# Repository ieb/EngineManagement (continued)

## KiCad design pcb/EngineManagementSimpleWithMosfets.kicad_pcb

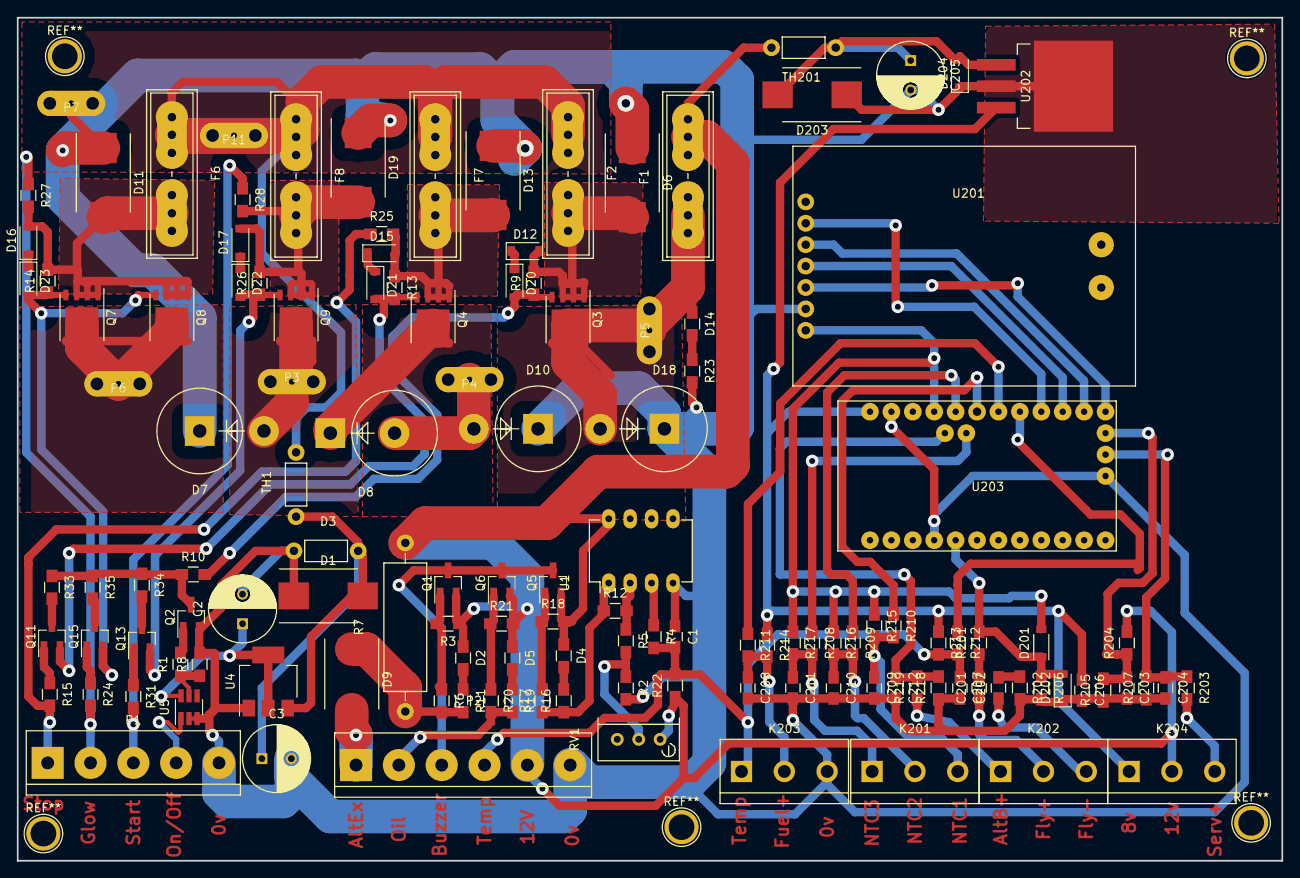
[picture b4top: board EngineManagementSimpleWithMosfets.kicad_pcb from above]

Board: 2 copper layers, 150.0 x 100.0 mm, 131 parts (0 on the bottom side), 77 nets.

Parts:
C1, C201, C202, C206, C207, C208, C209, C210, C211: 10nF; C_0805_HandSoldering
C2, C3: 10uF; C_Radial_D8_L11.5_P3.5
C203, C204, C212: 1nF; C_0805_HandSoldering
C205: 100uF; C_Radial_D8_L11.5_P3.5
D1, D6, D11, D13, D19, D203: SMBJ30CA-TR TSV; DO-214AB_Handsoldering
D2: ChargeWarn; R_0805_HandSoldering
D3: 10A100V; Resistor_Horizontal_RM7mm
D4: TempWarn; R_0805_HandSoldering
D5: OilWarn; R_0805_HandSoldering
D7, D18: 5A 600V; Diode_P600_Vertical_AnodeUp
D8: 10A 600V; Diode_P600_Vertical_KathodeUp
D9: 1A 40V; DO-214AB
D10: 10A 600V; Diode_P600_Vertical_AnodeUp
D12, D15, D16: ZENER; D_SOD-123
D14: PowerOn; R_0805_HandSoldering
D17: 10V Zeener; D_SOD-123
D20, D21, D22, D23: 1N4001; D_SOD-123
D201: 1N5819; SOD-123
D202, D204: 1N5819; D_SOD-123
F1: FUSE 5A; BladeFuse-CarType
F2: FUSE 30A; BladeFuse-CarType
F6, F8: FUSE 40A; BladeFuse-CarType
F7: FUSE 15A; BladeFuse-CarType
K201: Temps; bornier3
K202: FuelCool; bornier3
K203: FuelCoolAlt; bornier3
K204: Supply; bornier3
P1: VPButtons; bornier5
P2: ToEngine; bornier6
P3: StarterSolenoidT30; CrimpBlade
P4: StopSolenoid; CrimpBlade
P5: 12VSwitchedPower; CrimpBlade
P6: GlowPlugs; CrimpBlade
P7: 0v; CrimpBlade
P11: Battery+; CrimpBlade
Q1, Q5, Q6: BC807; SOT-23_Handsoldering
Q2: BS170; SOT-23_Handsoldering
Q3, Q4, Q7, Q8, Q9: SI7137; Si7137PowerPak
Q11, Q13, Q15: BS250P; SOT-23_Handsoldering
R1, R15, R24, R31: 100R; R_0805_HandSoldering
R2: 330R; R_0805_HandSoldering
R3, R4, R5, R8, R9, R17, R21, R25: 10K; R_0805_HandSoldering
R6, R18, R20, R27, R28: 2.2K; R_0805_HandSoldering
R7: 10R; Resistor_Horizontal_RM20mm
R10, R33, R34, R35: 220R; R_0805_HandSoldering
R11, R13, R14, R16, R19, R22, R23, R26, R213, R214: 1K; R_0805_HandSoldering
R12: 10M; R_0805_HandSoldering
R201, R202: 47K; R_0805_HandSoldering
R203, R204, R219: 1M; R_0805_HandSoldering
R205, R207, R218: 470K; R_0805_HandSoldering
R206, R208, R209, R210, R211, R212: 100K; R_0805_HandSoldering
R215, R216, R217: 4.7K; R_0805_HandSoldering
RV1: 20K; Potentiometer_Bourns_3296W_3-8Zoll_Inline_ScrewUp
TH1: THERMISTOR; Resistor_Horizontal_RM7mm
TH201: 500mA Thermistor; Resistor_Horizontal_RM7mm
U1: LM358; DIP-8_W7.62mm_LongPads
U4: NCP1117ST50T3G; SOT-223-3Lead_TabPin2
U5: Max16054; SOT-23-6_Handsoldering
U201: MCP2515Shield; MCP2515Board
U202: LM7808CT; TO-263-3Lead
U203: ArdinoMinPro; ArduinoProMini

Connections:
5V150mA: D201.2, R215.1, R216.1, R217.1, U201.7, U203.21
8V: C206.1, K204.1, R213.1, R214.1, U202.3, U203.24
12vSwitched: D2.1, D4.1, D5.1, F1.2, K204.2, P2.5, Q1.2, Q5.2, Q6.2, R3.1, R7.2, R18.2, R21.2, R22.1, R204.2, RV1.1, TH201.2, U1.8
AlternatorB+: K202.1, R219.1
AlternatorExcitation: D9.2, P2.1
Battery+: F2.1, F6.1, F7.1, F8.1, P11.1, TH1.2
Buzzer: P2.3, Q1.3, Q5.3, Q6.3
CANCS: U201.5, U203.13
CoolantTemp: C1.2, C207.1, K203.1, P2.4, R4.2, R22.2, R212.2, R213.2
Enable: Q2.3, R10.1, R33.1, R34.1, R35.1
Flywheel+: C201.1, K202.2
Flywheel-: C202.1, K202.3
FuelLevel+: C208.1, K203.2, R211.2, R214.2
GND: C1.1, C2.2, C3.2, C203.2, C204.2, C205.2, C206.2, C207.2, C208.2, C209.2, C210.2, C211.2, C212.2, D1.1, D3.1, D6.1, D7.1, D10.1, D11.1, D13.1, D18.1, D19.1, D202.1, D203.1, D204.1, K203.3, P1.5, P2.6, P7.1, Q2.2, R2.2, R8.2, R23.2, R202.2, R205.1, R206.2, R207.1, R218.1, U1.4, U4.1, U5.2, U5.3, U201.6, U202.2, U203.4, U203.23, U203.31
GlowBtn: P1.2, R24.2, R27.1
GlowPlugs: P6.1, Q7.3, Q8.3
MISO: U201.4, U203.15
MOSI: U201.3, U203.14
NTC1: C209.1, K201.3, R210.2, R215.2
NTC2: C210.1, K201.2, R209.2, R216.2
NTC3: C211.1, K201.1, R208.2, R217.2
unnamed: C2.1, U4.2, U5.6
unnamed: C3.1, D1.2, D3.2, TH1.1, U4.3
unnamed: C201.2, R201.1
unnamed: C202.2, R202.1
unnamed: C203.1, R204.1, R205.2, U203.A7
unnamed: C204.1, R203.1, R207.2, U203.A6
unnamed: C205.1, D203.2, D204.2, TH201.1, U202.1
unnamed: C212.1, R218.2, R219.2, U203.A5
unnamed: D2.2, R11.1
unnamed: D4.2, R16.2
unnamed: D5.2, R19.1
unnamed: D8.1, Q4.3
unnamed: D9.1, R6.2, R7.1, R11.2
unnamed: D11.2, D16.2, F6.2, Q7.2, Q8.2, R14.2, R27.2
unnamed: D12.1, D20.1
unnamed: D6.2, D12.2, F2.2, Q3.2, R9.2
unnamed: D13.2, D15.2, F7.2, Q4.2, R13.1, R25.2
unnamed: D14.1, D18.2, F1.1, P5.1, Q3.3
unnamed: D14.2, R23.1
unnamed: D15.1, D21.1
unnamed: D16.1, D23.1
unnamed: D17.1, D22.1
unnamed: D17.2, D19.2, F8.2, Q9.2, R26.2, R28.2
unnamed: D20.2, Q3.1, R9.1, R10.2
unnamed: D21.2, Q4.1, Q11.2, R13.2
unnamed: D22.2, Q9.1, Q13.2, R26.1
unnamed: D23.2, Q7.1, Q8.1, Q15.2, R14.1
unnamed: D201.1, D202.2, R201.2, R206.1, U203.5
unnamed: Q1.1, R3.2, R6.1
unnamed: Q2.1, R1.2
unnamed: Q5.1, R17.2, R18.1
unnamed: Q6.1, R20.1, R21.1
unnamed: Q11.1, R15.1
unnamed: Q11.3, R33.2
unnamed: Q13.1, R31.1
unnamed: Q13.3, R34.2
unnamed: Q15.1, R24.1
unnamed: Q15.3, R35.2
unnamed: R1.1, R8.1, U5.5
unnamed: R2.1, R5.2, RV1.2
unnamed: R4.1, U1.3
unnamed: R12.1, R16.1, R17.1, U1.1
unnamed: R5.1, R12.2, U1.2
unnamed: R208.1, U203.A4
unnamed: R209.1, U203.20
unnamed: R210.1, U203.19
unnamed: R211.1, U203.18
unnamed: R212.1, U203.17
OilSwitch: P2.2, R19.2, R20.2
OnOffBtn: P1.4, U5.1
SCK: U201.2, U203.16
ServiceBattery+: K204.3, R203.2
StartBtn: P1.3, R28.1, R31.2
StarterSolenoidT30: D7.2, P3.1, Q9.3
StopBtn: P1.1, R15.2, R25.1
StopSolenoid: D8.2, D10.2, P4.1

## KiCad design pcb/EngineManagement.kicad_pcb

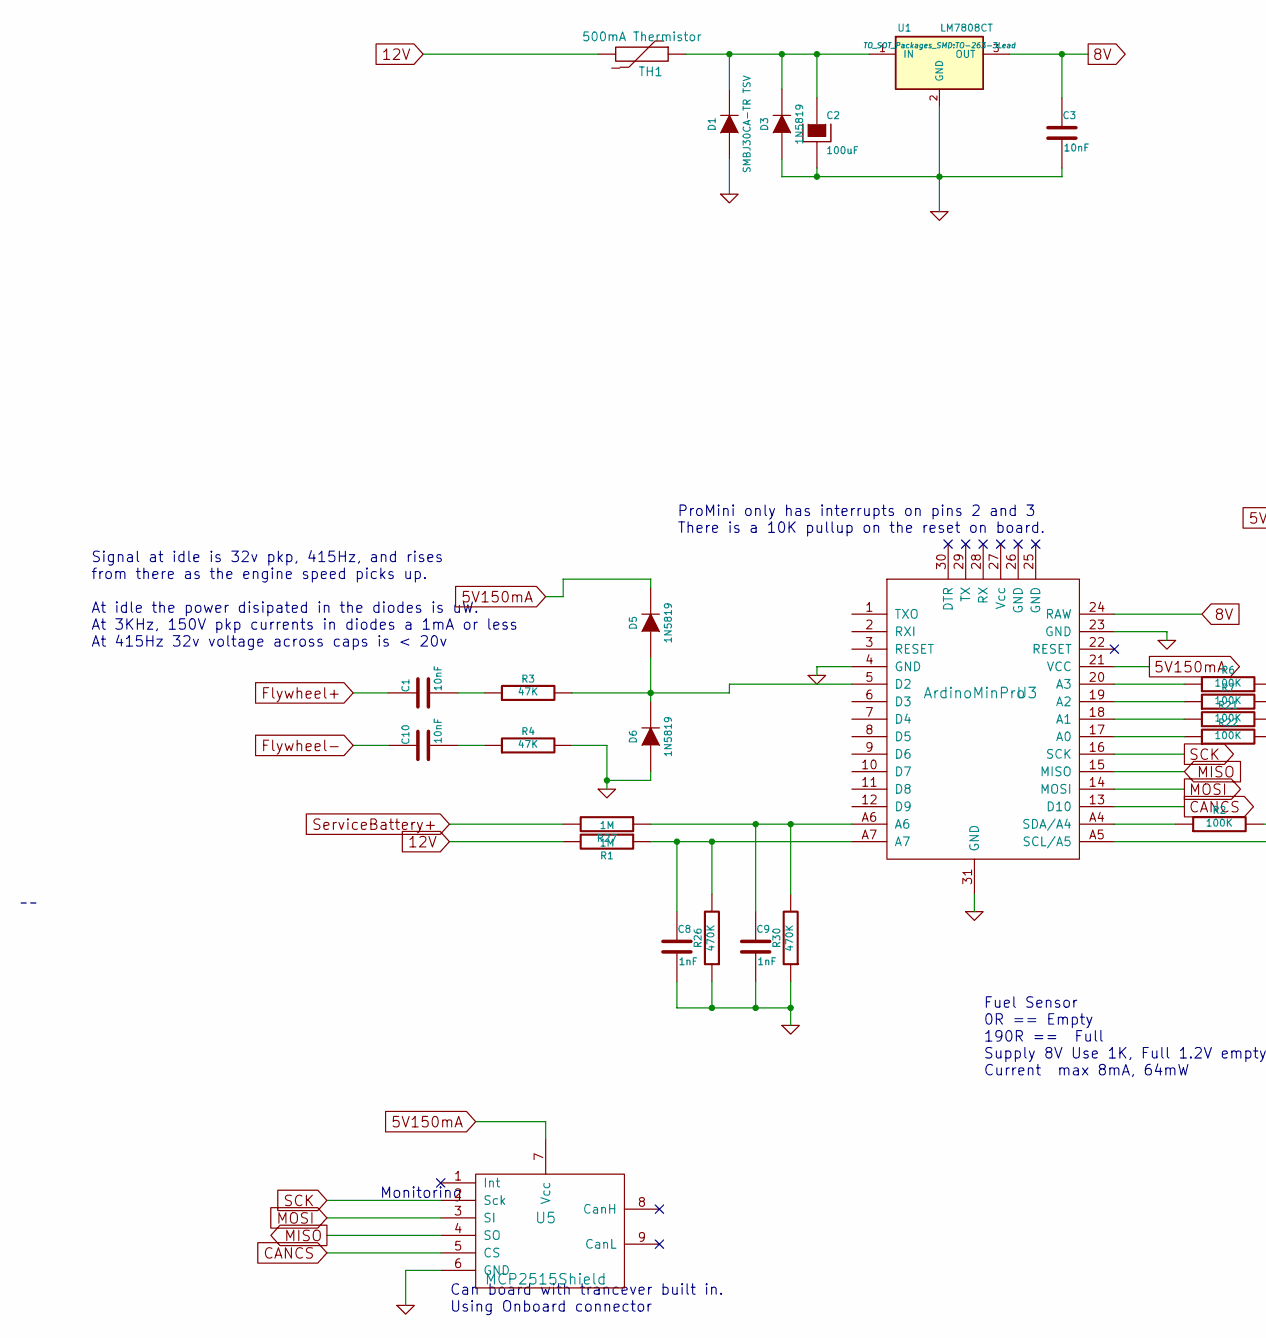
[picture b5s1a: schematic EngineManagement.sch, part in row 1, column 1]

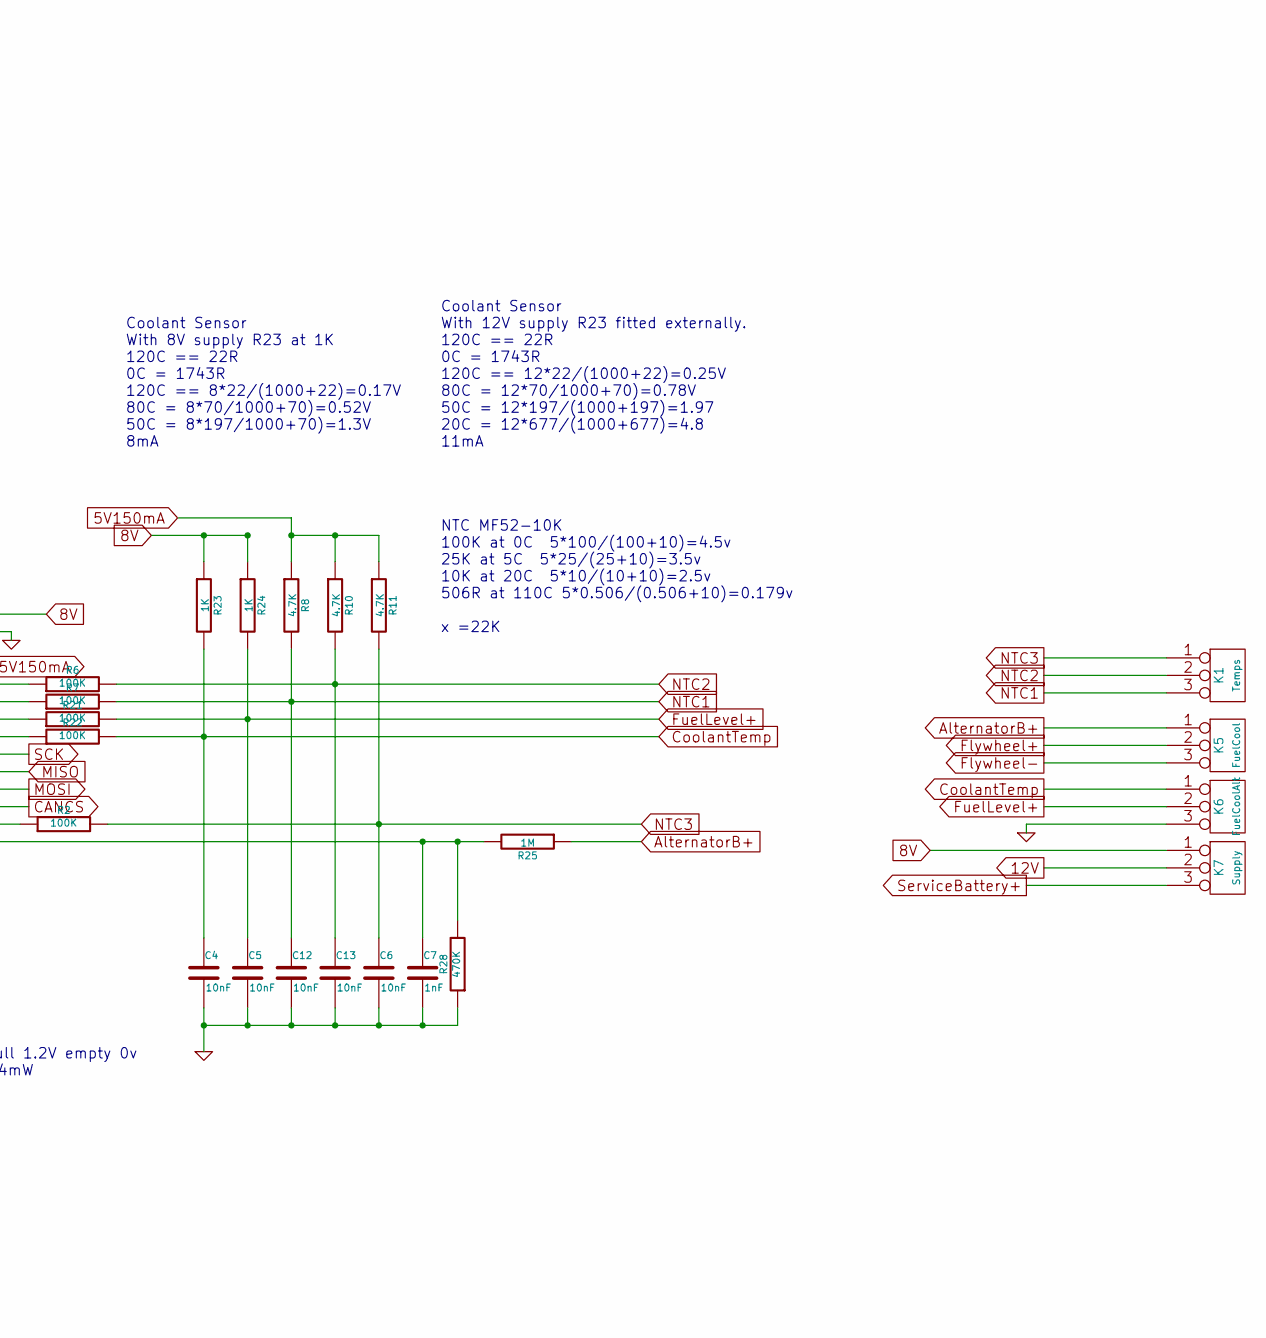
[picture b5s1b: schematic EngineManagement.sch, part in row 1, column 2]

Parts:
C1, C3, C4, C5, C6, C10, C12, C13: 10nF; C_0805_HandSoldering
C2: 100uF; C_Radial_D8_L11.5_P3.5
C7, C8, C9: 1nF; C_0805_HandSoldering
D1: SMBJ30CA-TR TSV; DO-214AB_Handsoldering
D3, D5, D6: 1N5819; Resistor_Horizontal_RM7mm
K1: Temps; bornier3
K5: FuelCool; bornier3
K6: FuelCoolAlt; bornier3
K7: Supply; bornier3
R1, R25, R27: 1M; R_0805_HandSoldering
R2, R6, R7, R21, R22: 100K; R_0805_HandSoldering
R3, R4: 47K; R_0805_HandSoldering
R8, R10, R11: 4.7K; R_0805_HandSoldering
R23, R24: 1K; R_0805_HandSoldering
R26, R28, R30: 470K; R_0805_HandSoldering
TH1: 500mA Thermistor; Resistor_Horizontal_RM7mm
U1: LM7808CT; TO-263-3Lead
U3: ArdinoMinPro; ArduinoProMini
U5: MCP2515Shield; MCP2515Board

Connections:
5V150mA: D5.2 (K), R8.1, R10.1, R11.1, U3.21 (VCC), U5.7 (Vcc); also elsewhere on the board
8V: C3.1, K7.1, R23.1, R24.1, U1.3 (OUT), U3.24 (RAW)
12V: K7.2 (PM), R1.2, TH1.2
AlternatorB+: K5.1, R25.1
CANCS: U3.13 (D10), U5.5 (CS)
CoolantTemp: C4.1, K6.1, R22.2, R23.2
Flywheel+: C1.1, K5.2 (PM)
Flywheel-: C10.1, K5.3
FuelLevel+: C5.1, K6.2 (PM), R21.2, R24.2
GND: C2.2, C3.2, C4.2, C5.2, C6.2, C7.2, C8.2, C9.2, C12.2, C13.2, D1.1 (A), D3.1 (A), D6.1 (A), K6.3, R4.2, R26.1, R28.1, R30.1, U1.2 (GND), U3.4 (GND), U3.23 (GND), U3.31 (GND), U5.6 (GND)
MISO: U3.15 (MISO), U5.4 (SO)
MOSI: U3.14 (MOSI), U5.3 (SI)
NTC1: C12.1, K1.3, R7.2, R8.2
NTC2: C13.1, K1.2 (PM), R6.2, R10.2
NTC3: C6.1, K1.1, R2.2, R11.2
unnamed: C1.2, R3.1
unnamed: C2.1, D1.2 (K), D3.2 (K), TH1.1, U1.1 (IN)
unnamed: C7.1, R25.2, R28.2, U3.A5 (SCL/A5)
unnamed: C8.1, R1.1, R26.2, U3.A7
unnamed: C9.1, R27.1, R30.2, U3.A6
unnamed: C10.2, R4.1
unnamed 21: D5.1 (A), D6.2 (K), R3.2, U3.5 (D2); also elsewhere on the board
unnamed: R2.1, U3.A4 (SDA/A4)
unnamed: R6.1, U3.20 (A3)
unnamed: R7.1, U3.19 (A2)
unnamed: R21.1, U3.18 (A1)
unnamed: R22.1, U3.17 (A0)
SCK: U3.16 (SCK), U5.2 (Sck)
ServiceBattery+: K7.3, R27.2

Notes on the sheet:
Monitoring
Fuel Sensor 0R == Empty 190R == Full Supply 8V Use 1K, Full 1.2V empty 0v Current max 8mA, 64mW
Coolant Sensor With 8V supply R23 at 1K 120C == 22R 0C = 1743R 120C == 8*22/(1000+22)=0.17V 80C = 8*70/1000+70)=0.52V 50C = 8*197/1000+70)=1.3V 8mA
Can board with trancever built in. Using Onboard connector
ProMini only has interrupts on pins 2 and 3 There is a 10K pullup on the reset on board.
Signal at idle is 32v pkp, 415Hz, and rises from there as the engine speed picks up. At idle the power disipated in the diodes is uW. At 3KHz, 150V pkp currents in diodes a 1mA or less At 415Hz 32v voltage across caps is < 20v
NTC MF52-10K 100K at 0C 5*100/(100+10)=4.5v 25K at 5C 5*25/(25+10)=3.5v 10K at 20C 5*10/(10+10)=2.5v 506R at 110C 5*0.506/(0.506+10)=0.179v x =22K
Coolant Sensor With 12V supply R23 fitted externally. 120C == 22R 0C = 1743R 120C == 12*22/(1000+22)=0.25V 80C = 12*70/1000+70)=0.78V 50C = 12*197/(1000+197)=1.97 20C = 12*677/(1000+677)=4.8 11mA

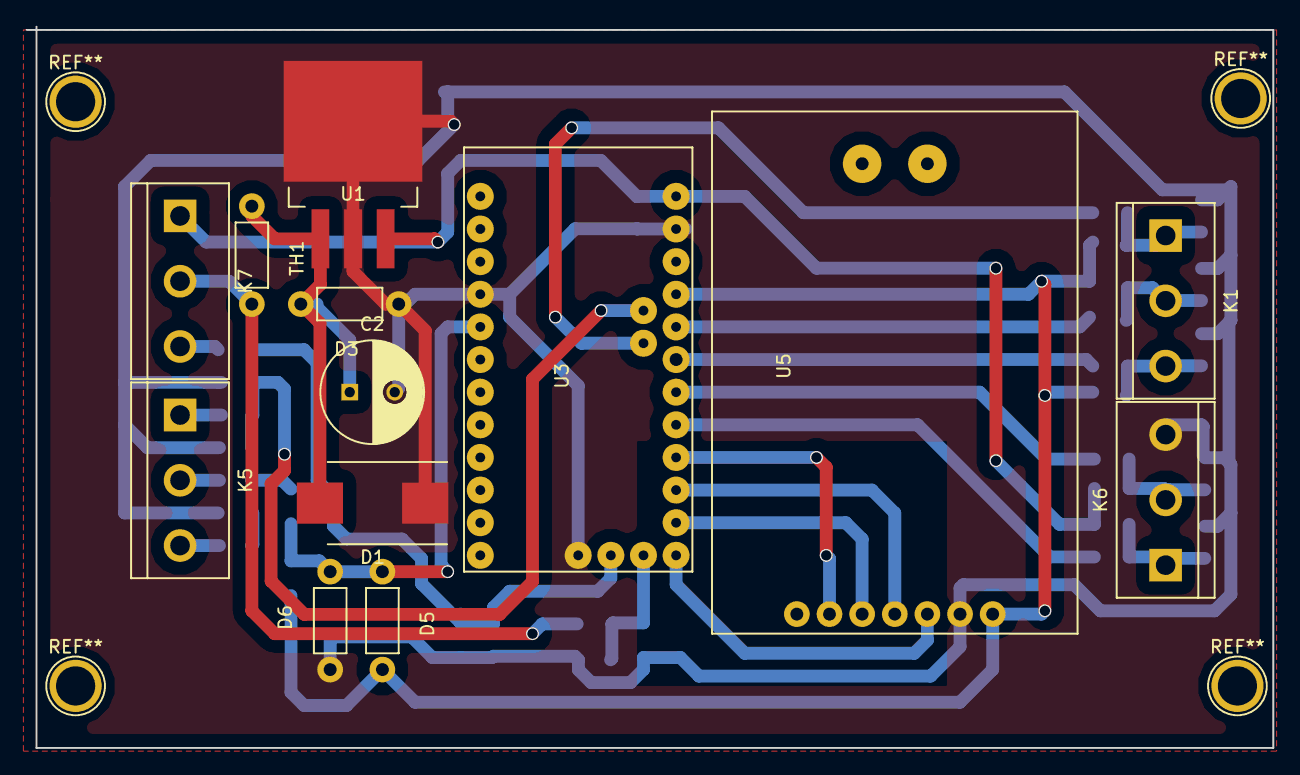
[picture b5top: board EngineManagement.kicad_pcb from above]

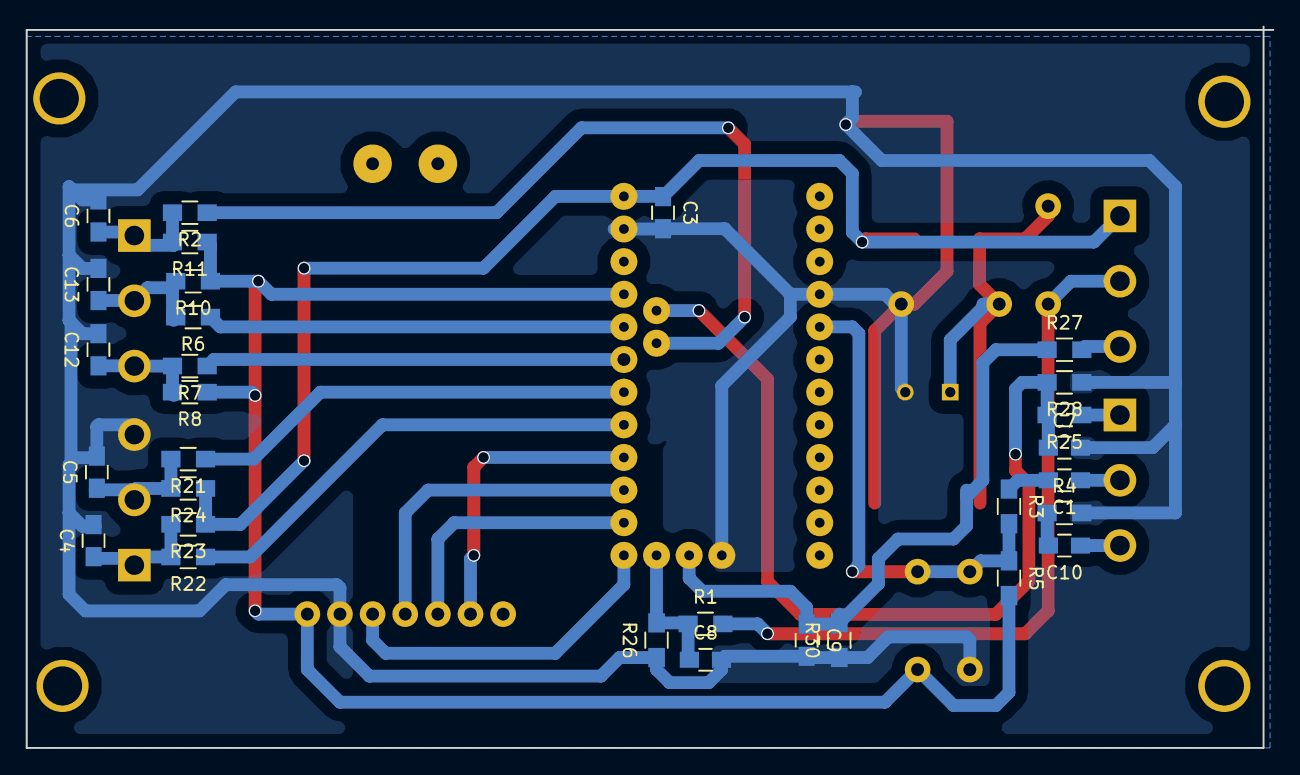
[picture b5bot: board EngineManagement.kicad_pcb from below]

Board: 2 copper layers, 97.0 x 56.1 mm, 43 parts (30 on the bottom side), 29 nets.

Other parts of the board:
R5: 10K; R_0805_HandSoldering

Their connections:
5V150mA: R5.2; also elsewhere on the board
unnamed 21: R5.1; also elsewhere on the board

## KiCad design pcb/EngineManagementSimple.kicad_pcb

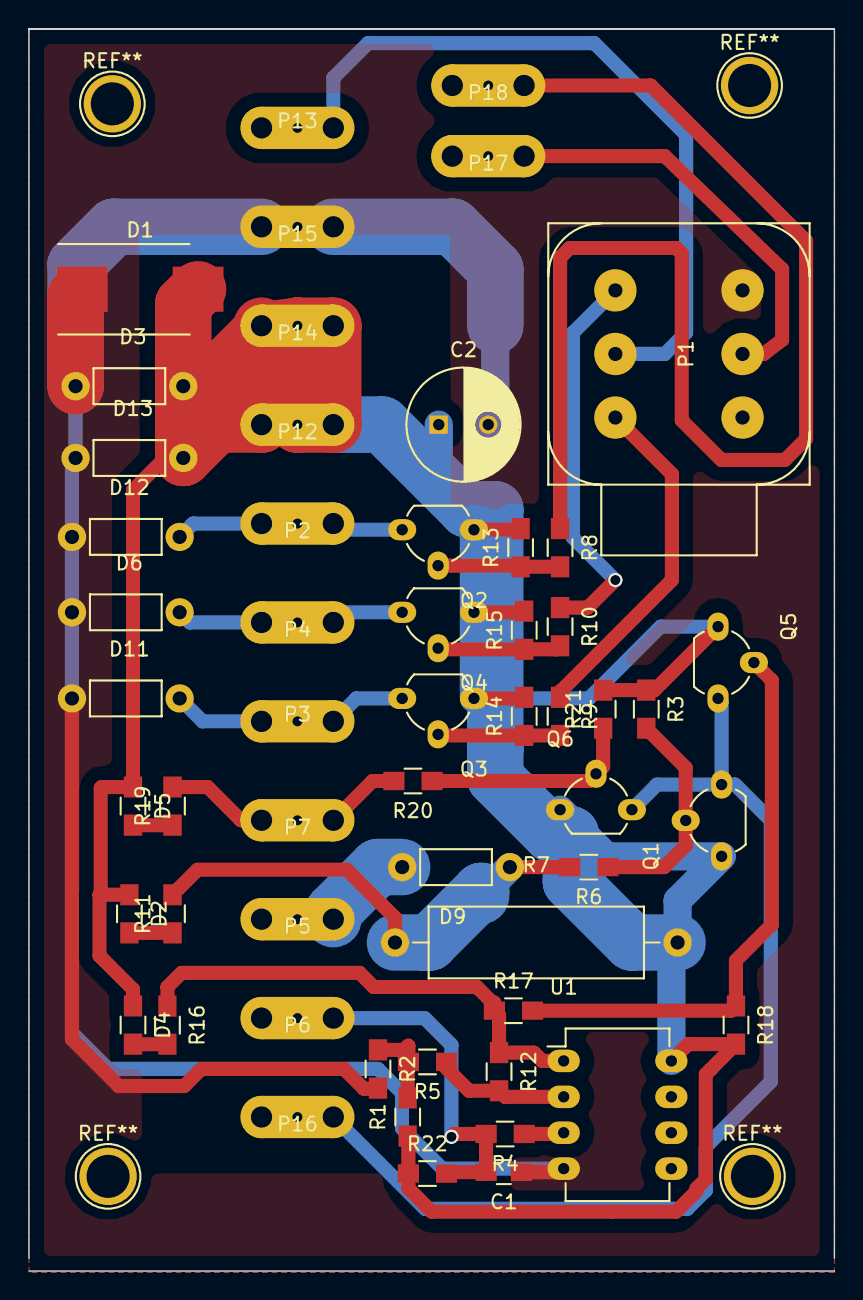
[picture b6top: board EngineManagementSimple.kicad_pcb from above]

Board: 2 copper layers, 57.0 x 87.9 mm, 55 parts (0 on the bottom side), 28 nets.

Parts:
C1: 10nF; C_0805_HandSoldering
C2: 100uF; C_Radial_D8_L11.5_P3.5
D1: SMBJ30CA-TR TSV; DO-214AB_Handsoldering
D2: ChargeWarn; R_0805_HandSoldering
D3: 10A100V; Resistor_Horizontal_RM7mm
D4: TempWarn; R_0805_HandSoldering
D5: OilWarn; R_0805_HandSoldering
D6, D11, D12, D13: 5A 600V; Resistor_Horizontal_RM7mm
D9: 1A 40V; Resistor_Horizontal_RM7mm
P1: VPButtons; DeutchDT06
P2: StartCoil; CrimpBlade
P3: StopCoil; CrimpBlade
P4: GlowCoil; CrimpBlade
P5: Excitation; CrimpBlade
P6: CoolantTemp; CrimpBlade
P7: OilSwitch; CrimpBlade
P12: 12VSwitched; CrimpBlade
P13: OnOffTrigger; CrimpBlade
P14: 12vSwitchedIn; CrimpBlade
P15: 0v; CrimpBlade
P16: Buzzer; CrimpBlade
P17: Neutral-; CrimpBlade
P18: Neutral+; CrimpBlade
Q1, Q2, Q3, Q4, Q5, Q6: 2N2907; TO-92_Molded_Wide_Oval
R1, R11, R16, R19, R22: 1K; R_0805_HandSoldering
R2: 33R; R_0805_HandSoldering
R3, R4, R5, R13, R14, R15, R18, R21: 10K; R_0805_HandSoldering
R6, R8, R9, R10, R17, R20: 2.2K; R_0805_HandSoldering
R7: 10R; Resistor_Horizontal_RM20mm
R12: 100K; R_0805_HandSoldering
U1: LM358; DIP-8_W7.62mm_LongPads

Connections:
12vSwitched: C2.1, D1.2, D2.1, D3.2, D4.1, D5.1, D13.2, P12.1, P14.1, Q1.1, Q2.1, Q3.1, Q4.1, Q5.1, Q6.1, R1.1, R3.1, R7.2, R13.2, R14.2, R15.2, R18.2, R21.2, R22.1, U1.8
AlternatorExcitation: D9.2, P5.1
Buzzer: P16.1, Q1.3, Q5.3, Q6.3
CoolantTemp: C1.2, P6.1, R4.2, R22.2
GND: C1.1, C2.2, D1.1, D3.1, D6.1, D11.1, D12.1, D13.1, P1.4, P15.1, R2.2, U1.4
GlowBtn: P1.3, R10.1
GlowCoil: D6.2, P4.1, Q4.3
unnamed: D2.2, R11.1
unnamed: D4.2, R16.2
unnamed: D5.2, R19.1
unnamed: D9.1, R6.2, R7.1, R11.2
unnamed: Q1.2, R3.2, R6.1
unnamed: Q2.2, R8.2, R13.1
unnamed: Q3.2, R9.2, R14.1
unnamed: Q4.2, R10.2, R15.1
unnamed: Q5.2, R17.2, R18.1
unnamed: Q6.2, R20.1, R21.1
unnamed: R1.2, R2.1, R5.2
unnamed: R4.1, U1.3
unnamed: R12.1, R16.1, R17.1, U1.1
unnamed: R5.1, R12.2, U1.2
Neutral+: P18.1, R8.1
Neutral-: P1.5, P17.1
OilSwitch: P7.1, R19.2, R20.2
OnOffBtn: P1.2, P13.1
StartCoil: D12.2, P2.1, Q2.3
StopBtn: P1.1, R9.1
StopCoil: D11.2, P3.1, Q3.3

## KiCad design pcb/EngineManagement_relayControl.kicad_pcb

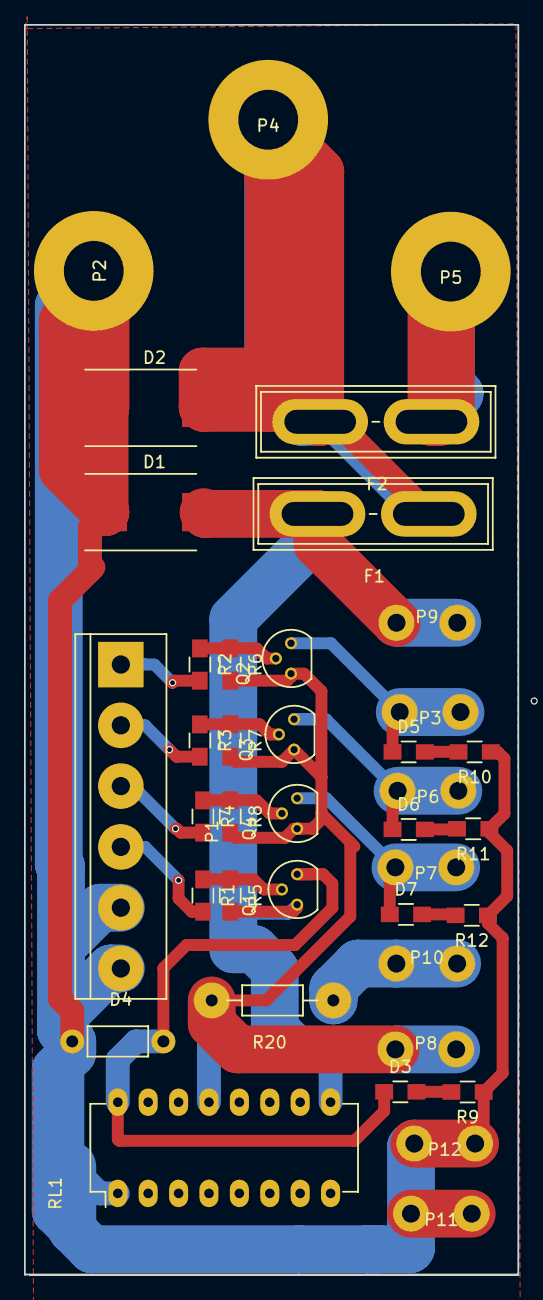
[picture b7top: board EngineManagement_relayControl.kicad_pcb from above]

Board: 2 copper layers, 41.2 x 104.5 mm, 39 parts (0 on the bottom side), 22 nets.

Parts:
D1, D2: SMBJ30CA-TR TSV; DO-214AB_Handsoldering
D3, D5, D6, D7: LED; R_0805_HandSoldering
D4: 1N5819; Resistor_Horizontal_RM7mm
F1: FUSE 5A; BladeFuse-CarType
F2: FUSE 40A; BladeFuse-CarType
P1: Buttons; bornier6
P2: 0V; M5Bolt
P3: StartRelay; CrimpBlade
P4: 12VFused; M5Bolt
P5: 12VIn; M5Bolt
P6: StopRelay; CrimpBlade
P7: GlowRelay; CrimpBlade
P8: 12VSwitched; CrimpBlade
P9: 12VProtected; CrimpBlade
P10: Excitation; CrimpBlade
P11, P12: 0V; CrimpBlade
Q1, Q2, Q3, Q4: 2N2907; TO-92_Molded_Narrow
R1, R2, R3, R4: 1K; R_0805_HandSoldering
R5, R6, R7, R8, R9, R10, R11, R12: 10K; R_0805_HandSoldering
R20: Bulb 12v5W or resistor; Resistor_Horizontal_RM10mmLargePads
RL1: HFD2; DIP-16_W7.62mm_LongPads

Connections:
Battery+: D2.2, F1.1, F2.2, P4.1
BatteryProtected+: D1.2, F1.2, P9.1, Q1.1, R5.2, RL1.9
BatterySwitched+: P8.1, Q2.1, Q3.1, Q4.1, R6.2, R7.2, R8.2, R20.2, RL1.13
BatteryUnfused+: F2.1, P5.1
Excitation: P10.1, R20.1
GND: D1.1, D2.1, D4.1, P1.5, P1.6, P2.1, P11.1, P12.1, R9.1, R10.1, R11.1, R12.1, RL1.1
Glow: D7.1, P7.1, Q4.3
GlowBtn: P1.3, R4.2
unnamed: D3.1, D4.2, Q1.3, RL1.16
unnamed: D3.2, R9.2
unnamed: D5.2, R10.2
unnamed: D6.2, R11.2
unnamed: D7.2, R12.2
unnamed: Q1.2, R1.1, R5.1
unnamed: Q2.2, R2.1, R6.1
unnamed: Q3.2, R3.1, R7.1
unnamed: Q4.2, R4.1, R8.1
OnOffBtn: P1.4, R1.2
Start: D5.1, P3.1, Q2.3
StartBtn: P1.1, R2.2
Stop: D6.1, P6.1, Q3.3
StopBtn: P1.2, R3.2

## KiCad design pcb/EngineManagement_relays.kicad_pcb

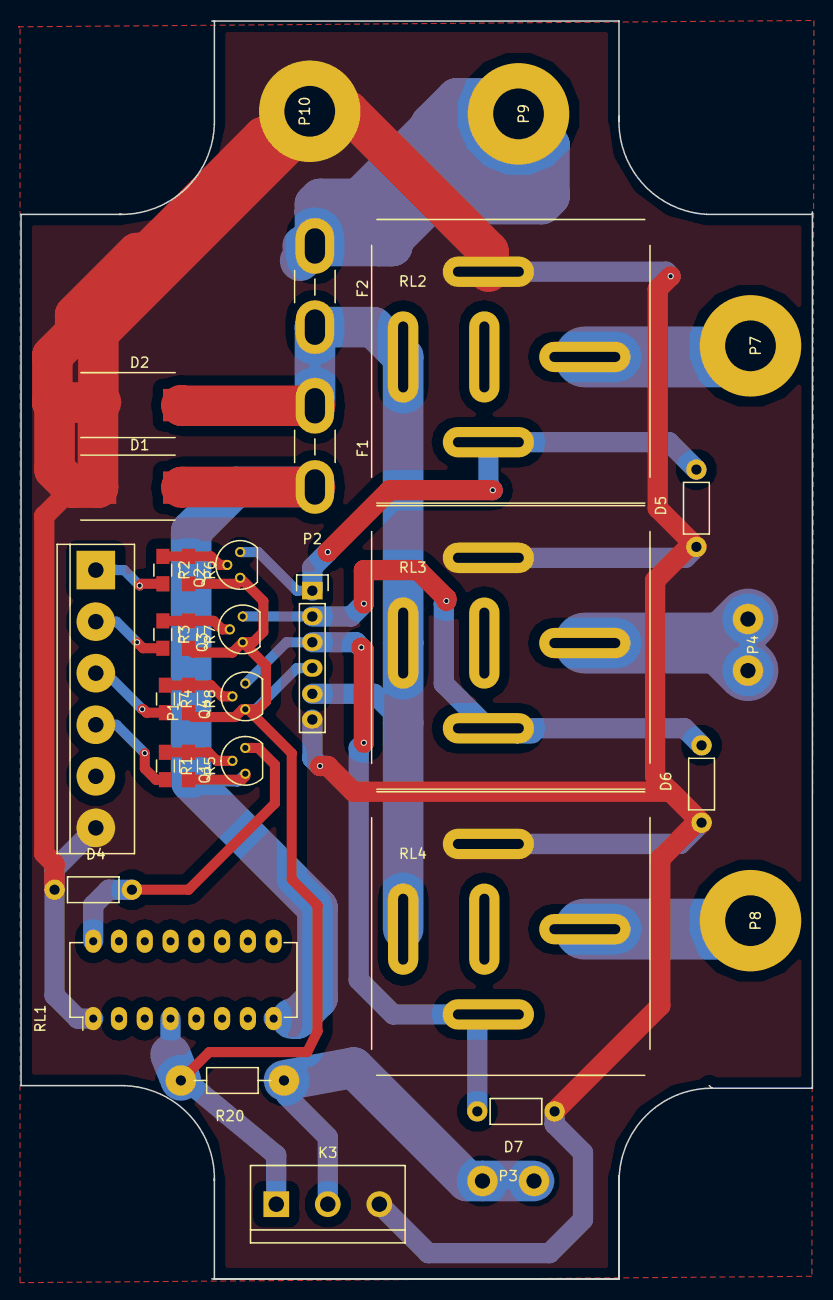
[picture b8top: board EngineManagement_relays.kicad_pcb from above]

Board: 2 copper layers, 78.0 x 124.0 mm, 34 parts (0 on the bottom side), 21 nets.

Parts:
D1, D2: SMBJ30CA-TR TSV; DO-214AB_Handsoldering
D4, D5, D6, D7: 1N5819; Resistor_Horizontal_RM7mm
F1: FUSE 5A; BladeFuse-Mini
F2: FUSE 40A; BladeFuse-Mini
K3: ToMCU; bornier3
P1: Buttons; bornier6
P2: EmergencyButtons; Pin_Header_Straight_1x06
P3: Excitation; CrimpBlade
P4: Stop; CrimpBlade
P7: StarterT30; M5Bolt
P8: Glow; M5Bolt
P9: 12V; M5Bolt
P10: 0V; M5Bolt
Q1, Q2, Q3, Q4: 2N2907; TO-92_Molded_Narrow
R1, R2, R3, R4: 1K; R_0805_HandSoldering
R5, R6, R7, R8: 10K; R_0805_HandSoldering
R20: Bulb 12v5W or resistor; Resistor_Horizontal_RM10mmLargePads
RL1: HFD2; DIP-16_W7.62mm_LongPads
RL2, RL3, RL4: AutomotiveRelay; AutomotiveRelay35A

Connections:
Battery+: D2.2, F1.1, F2.2, P2.5, RL2.87, RL3.87, RL4.87
BatteryProtected+: D1.2, F1.2, Q1.1, R5.2, RL1.8
BatterySwitched+: K3.1, P2.4, Q2.1, Q3.1, Q4.1, R6.2, R7.2, R8.2, R20.2, RL1.4
BatteryUnfused+: F2.1, P9.1
Excitation: K3.2, P3.1, R20.1
FuelLevel-: D1.1, D2.1, D4.1, D5.1, D6.1, D7.1, K3.3, P1.6, P2.6, P10.1, RL1.1, RL2.85, RL3.85, RL4.85
GlowBtn: P1.3, R4.2
GlowBtnDirect: D7.2, P2.3, Q4.3, RL4.86
GlowPlugs: P8.1, RL4.30
unnamed: D4.2, Q1.3, RL1.16
unnamed: Q1.2, R1.1, R5.1
unnamed: Q2.2, R2.1, R6.1
unnamed: Q3.2, R3.1, R7.1
unnamed: Q4.2, R4.1, R8.1
OnOffBtn: P1.4, R1.2
StartBtn: P1.1, R2.2
StartBtnDirect: D5.2, P2.1, Q2.3, RL2.86
StarterMotorT30: P7.1, RL2.30
StopBtn: P1.2, R3.2
StopBtnDirect: D6.2, P2.2, Q3.3, RL3.86
StopSolenoid: P4.1, RL3.30

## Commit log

2021-08-16 Initial commit, v1 board running, testing
2021-08-17 Added readme
2021-08-17 Fixed display
2021-08-20 Before using edge triggers for onoff
2021-08-22 VP Tacho has blown Can drivers on custom ASIC, plan aborted
2021-09-07 Redesigned to not use VP J1939 instruments
2021-09-09 NTC sensors working correctly
2021-09-12 Ready for installation
2021-09-12 Added pdfs for reference
2021-09-13 Removed HandleCommandedAdres as PGN65240 is only multi packet
2021-10-01 Added mosfet based board
2021-10-17 After testing, fixed a number of things
2021-10-25 First version on SNMEA2000 library, still testing
2021-10-25 Fixed sending product info and byte orders
2021-10-26 Fixed masks and filters
2021-10-27 Fixed some output encoding errors
2021-10-27 Cleanup unused files
2021-10-28 Extracted sensors into a class
2021-11-28 Istalled working version, all working, may need some adjustment on messages
2021-12-29 Dixed sequence ID errors, added dsign for PiCan board
2021-12-29 Mistook instance for sid, fixed
2021-12-30 Missed fastpacket sequence counter
2022-07-15 Reorged pcbs and brought NMEA2000 improvements in from CanPressure via lib
2023-09-09 Fixed 49day overflows
2024-04-17 Fixes to output messages, and spell check
